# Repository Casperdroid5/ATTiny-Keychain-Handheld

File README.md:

# ATTiny Keychain Handheld

The ATTiny Keychain Handheld is an open-source project aimed at creating a compact and portable handheld device using the ATTiny microcontroller. This project provides a platform for hobbyists and electronics enthusiasts to build their own handheld device for various purposes such as gaming, basic applications, or custom projects.

## Features

- Compact and portable design
- ATTiny microcontroller
- OLED display
- User input
- Programmable
- Open-source

## Usage

To use the ATTiny Keychain Handheld, follow these steps:

1. Clone or download the project repository from [GitHub](https://github.com/Casperdroid5/ATTiny-Keychain-Handheld).
2. Gather the necessary components and tools required for building the handheld device.
3. Assemble the device following the step-by-step instructions provided in the documentation.
4. Upload the firmware code to the ATTiny microcontroller using the provided programming instructions.
5. Customize the device as desired by modifying the firmware code or the design files for the enclosure.

## Documentation

Detailed documentation and guides on how to build and customize the handheld device can be found in the [Documentation](https://github.com/Casperdroid5/ATTiny-Keychain-Handheld/tree/main/Documentation) directory of the project repository. The documentation includes component lists, PCB design and circuit diagrams.

## Contributing

Contributions to the ATTiny Keychain Handheld project are welcome. If you find any issues, have suggestions for improvements, or want to contribute new features, please refer to the [Contributing](https://github.com/Casperdroid5/ATTiny-Keychain-Handheld/tree/main/Contributing) directory in the project repository.

## License

The ATTiny Keychain Handheld project is released under the [MIT License](https://github.com/Casperdroid5/ATTiny-Keychain-Handheld/blob/main/LICENSE).

## Conclusion

The ATTiny Keychain Handheld project offers an exciting opportunity for electronics enthusiasts and hobbyists to build their own portable handheld device. With its compact design, ATTiny microcontroller, and open-source nature, the project provides a versatile platform for creating various applications and games. Whether you are a beginner or an experienced developer, this project encourages exploration and customization.

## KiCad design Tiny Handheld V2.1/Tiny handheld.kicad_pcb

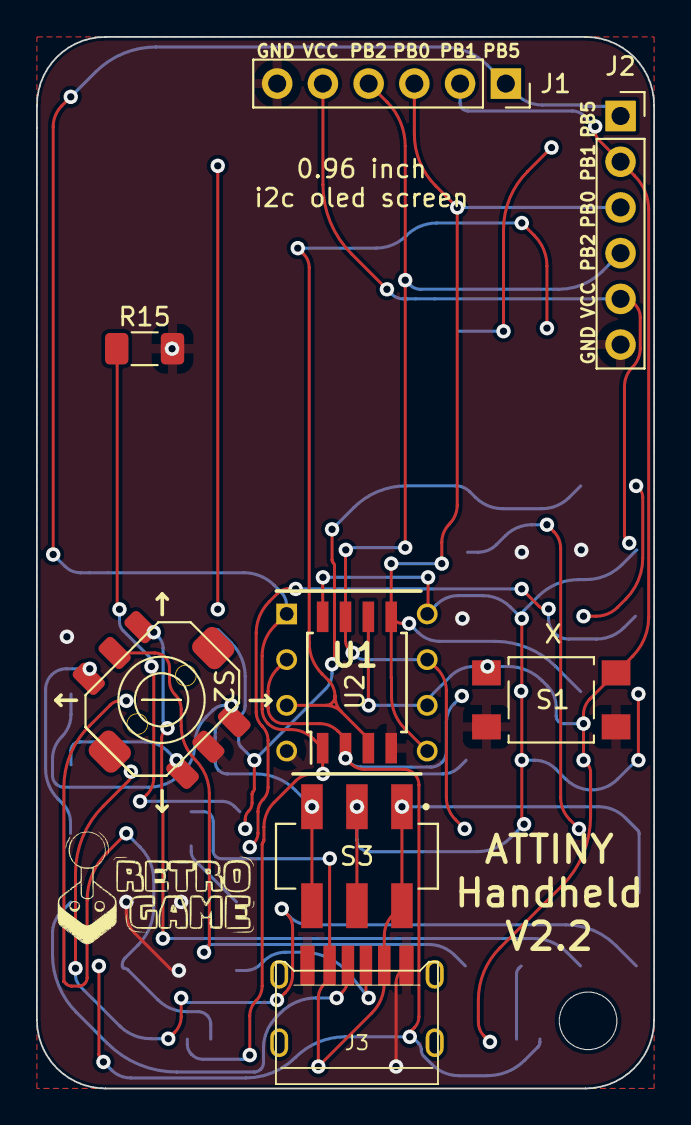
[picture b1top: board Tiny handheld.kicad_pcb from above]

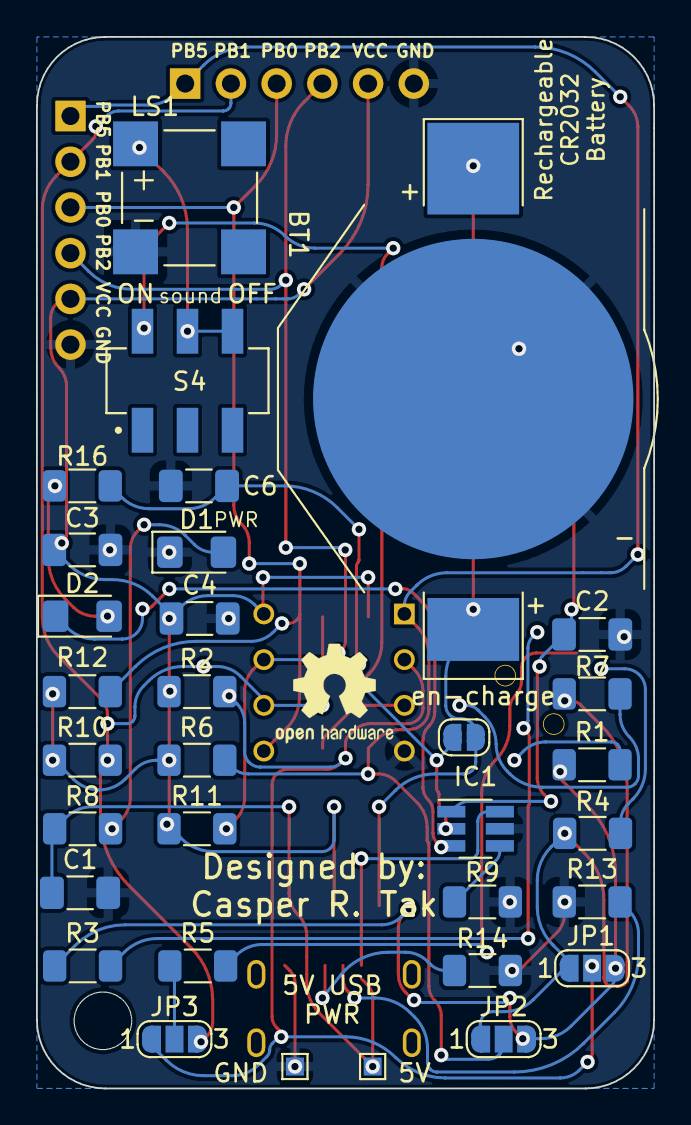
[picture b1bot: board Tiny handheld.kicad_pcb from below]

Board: 2 copper layers, 34.3 x 58.4 mm, 42 parts (32 on the bottom side), 27 nets.

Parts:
5V: 5V; TestPoint_Pad_1.0x1.0mm
BT1: Battery_Cell; BatteryHolder_Keystone_3002_1x2032
C1: 1uF 16V; C_1206_3216Metric_Pad1.33x1.80mm_HandSolder
C2: 1uF; C_1206_3216Metric_Pad1.33x1.80mm_HandSolder
C3: 47uF; C_1206_3216Metric_Pad1.33x1.80mm_HandSolder
C4: 100nF; C_1206_3216Metric_Pad1.33x1.80mm_HandSolder
C6: 2.2uF 16V; C_1206_3216Metric_Pad1.33x1.80mm_HandSolder
D1, D2: LED; LED_1206_3216Metric_Pad1.42x1.75mm_HandSolder
GND: GND; TestPoint_Pad_1.0x1.0mm
H1: MountingHole; MountingHole_3.2mm_M3
IC1: BQ21040DBVR; SOT-23-6_Handsoldering
J1: VDisplay/prog1; PinSocket_1x06_P2.54mm_Vertical
J2: HDisplay/prog; PinSocket_1x06_P2.54mm_Vertical
J3: USB_C_Receptacle_USB2.0; TYPE-C-31-M-17_handsolder
JP1, JP2, JP3: SolderJumper_3_Bridged123; SolderJumper-3_P1.3mm_Open_RoundedPad1.0x1.5mm_NumberLabels
LS1: KSSGK4B16-20; XDCR_KSSGK4B16-20
R1, R4: 88k; R_1206_3216Metric_Pad1.30x1.75mm_HandSolder
R2, R6: 22k; R_1206_3216Metric_Pad1.30x1.75mm_HandSolder
R3, R5, R7: 33k; R_1206_3216Metric_Pad1.30x1.75mm_HandSolder
R8, R16: 470; R_1206_3216Metric_Pad1.30x1.75mm_HandSolder
R9: 11k; R_1206_3216Metric_Pad1.30x1.75mm_HandSolder
R10: 10k; R_1206_3216Metric_Pad1.30x1.75mm_HandSolder
R11, R12: 4k7; R_1206_3216Metric_Pad1.30x1.75mm_HandSolder
R13, R14: 5k1; R_1206_3216Metric_Pad1.30x1.75mm_HandSolder
R15: 10k NTC; R_1206_3216Metric_Pad1.30x1.75mm_HandSolder
S1: MOMENTARY-SWITCH-SPST-2-SMD-5.2MM; SW_SPST_TL3305B
S2: JOYSTICK_MINI; 5 way button (joystick)
S3, S4: JS202011SCQN; SW_JS202011SCQN
U1: ATtiny85-20P; DIP781W56P254L950H533Q8N
U2: ATtiny85-20S; SOIC-8W_5.3x5.3mm_P1.27mm
en-charge: Jumper_2_Open; SolderJumper-2_P1.3mm_Open_RoundedPad1.0x1.5mm

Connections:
BatOut: BT1.1 (+), S3.3, S3.6, en-charge.2 (B)
ExtVCC: 5V.1, C1.1, IC1.6 (VIN), J3.A9 (VBUS), J3.B9 (VBUS), R8.1, S3.1, S3.4
GND: BT1.2 (-), C1.2, C2.2, C3.2, C4.2, C6.2, D1.1 (K), GND.1, IC1.5 (GND), J1.6, J2.6, J3.A12 (GND), J3.B12 (GND), LS1.N, R9.2, R13.1, R14.1, R15.2, S1.1, S1.2, S2.GND, U1.4 (GND), U2.4 (GND)
unnamed: C2.1, IC1.1 (TS), R15.1
unnamed: C6.1, IC1.2 (OUT), R16.1, en-charge.1 (A)
unnamed: D1.2 (A), R8.2
unnamed: D2.1 (K), IC1.3 (~CHG)
unnamed: D2.2 (A), R16.2
unnamed: IC1.4 (ISET), R9.1
unnamed: J3.A5 (CC1), R13.2
unnamed: J3.B5 (CC2), R14.2
unnamed: JP1.1 (A), JP2.1 (A), R4.1, R7.1
unnamed: JP1.3 (B), JP2.3 (B), R1.1, R3.1
unnamed: JP3.2 (C), R5.1
unnamed: LS1.P, S4.5, S4.6
unnamed: R1.2, S2.DOWN
unnamed: R3.2, S2.UP
unnamed: R4.2, S2.LEFT
unnamed: R5.2, S2.CTR (CENT)
unnamed: R7.2, S2.RIGHT
PB0/SDA/MOSI: J1.3, J2.3, R12.2, U1.5 (AREF/PB0), U2.5 (AREF/PB0)
PB1/MISO: J1.2, J2.2, JP3.3 (B), R10.2, S1.3, S1.4, U1.6 (PB1), U2.6 (PB1)
PB2/SCL/SCK: J1.4, J2.4, R11.2, U1.7 (PB2), U2.7 (PB2)
PB3: JP1.2 (C), JP3.1 (A), R2.2, U1.2 (XTAL1/PB3), U2.2 (XTAL1/PB3)
PB4: S4.4, U1.3 (XTAL2/PB4), U2.3 (XTAL2/PB4)
PB5/RES: J1.1, J2.1, JP2.2 (C), R6.2, U1.1 (~RESET/PB5), U2.1 (~RESET/PB5)
VCC: C3.1, C4.1, J1.5, J2.5, R2.1, R6.1, R10.1, R11.1, R12.1, S3.2, S3.5, U1.8 (VCC), U2.8 (VCC)

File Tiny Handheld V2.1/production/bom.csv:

Designator,Footprint,Quantity,Value,LCSC Part #
5V,TestPoint_Pad_1.0x1.0mm,1,5V,
BT1,BatteryHolder_Keystone_3002_1x2032,1,Battery_Cell,
C1,C_1206_3216Metric_Pad1.33x1.80mm_HandSolder,1,1uF 16V,
C2,C_1206_3216Metric_Pad1.33x1.80mm_HandSolder,1,1uF,
C3,C_1206_3216Metric_Pad1.33x1.80mm_HandSolder,1,47uF,
C4,C_1206_3216Metric_Pad1.33x1.80mm_HandSolder,1,100nF,
C6,C_1206_3216Metric_Pad1.33x1.80mm_HandSolder,1,2.2uF 16V,
"D1, D2",LED_1206_3216Metric_Pad1.42x1.75mm_HandSolder,2,LED,
GND,TestPoint_Pad_1.0x1.0mm,1,GND,
H1,MountingHole_3.2mm_M3,1,MountingHole,
IC1,SOT-23-6_Handsoldering,1,BQ21040DBVR,
J1,PinSocket_1x06_P2.54mm_Vertical,1,VDisplay/prog1,
J2,PinSocket_1x06_P2.54mm_Vertical,1,HDisplay/prog,
J3,TYPE-C-31-M-17_handsolder,1,USB_C_Receptacle_USB2.0,
"JP1, JP2, JP3",SolderJumper-3_P1.3mm_Open_RoundedPad1.0x1.5mm_NumberLabels,3,SolderJumper_3_Bridged123,
LS1,XDCR_KSSGK4B16-20,1,KSSGK4B16-20,
"R1, R4",R_1206_3216Metric_Pad1.30x1.75mm_HandSolder,2,88k,
R10,R_1206_3216Metric_Pad1.30x1.75mm_HandSolder,1,10k,
"R11, R12",R_1206_3216Metric_Pad1.30x1.75mm_HandSolder,2,4k7,
"R13, R14",R_1206_3216Metric_Pad1.30x1.75mm_HandSolder,2,5k1,
R15,R_1206_3216Metric_Pad1.30x1.75mm_HandSolder,1,10k NTC,
"R16, R8",R_1206_3216Metric_Pad1.30x1.75mm_HandSolder,2,470,
"R2, R6",R_1206_3216Metric_Pad1.30x1.75mm_HandSolder,2,22k,
"R3, R5, R7",R_1206_3216Metric_Pad1.30x1.75mm_HandSolder,3,33k,
R9,R_1206_3216Metric_Pad1.30x1.75mm_HandSolder,1,11k,
S1,SW_SPST_TL3305B,1,MOMENTARY-SWITCH-SPST-2-SMD-5.2MM,
S2,5 way button (joystick),1,JOYSTICK_MINI,
"S3, S4",SW_JS202011SCQN,2,JS202011SCQN,
U1,DIP781W56P254L950H533Q8N,1,ATtiny85-20P,
U2,SOIC-8W_5.3x5.3mm_P1.27mm,1,ATtiny85-20S,
en-charge,SolderJumper-2_P1.3mm_Open_RoundedPad1.0x1.5mm,1,Jumper_2_Open,

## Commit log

2022-09-16 First commit of tiny handheld
2022-09-16 designed custom 5 way button and finished up footprint assignment
2022-09-16 removed errors (ERC)
    Left warnings in
2022-09-16 added missing button footprint
2022-09-16 updated usb c port schematic
2022-09-16 updated footprint on attiny 85 and removed backup zip files
2022-09-16 fixed footprint error U2
    Changed the values back to the original
2022-09-16 added different switch in schematic
2022-09-16 fixed ERC error
2022-09-16 changed switch for audio toggle
2022-09-16 removed all errors from pcb new
    Ready to start pcb design
2022-09-16 changed speaker footprint and updated it
2022-09-16 first layout tryout
2022-09-16 layout improved
2022-09-16 improved layout and added silkscreen
2022-09-17 updated schematic (nothing special)
2022-09-17 removed vertical screen header
2022-09-17 started routing
2022-09-17 continued wiring
2022-09-17 more connections made
2022-09-17 all errors (that i found critical) resolved
2022-09-17 board cleanup
2022-09-17 first melted circuit tryout (rounded tracks)
2022-09-17 removed fluid traces, First functional design
2022-09-17 V1.0
    Added silkscreen and finished up with straight lines (no curves yet)
2022-09-17 Added curvy wires
    Because they are the best thing in this straight world
2022-09-17 updated page settings (kicad)
2022-09-17 gerber files added
2022-09-17 New gerber files
2022-09-17 Fixed gerber files
    can be uploaded directly to easyeda
2022-09-17 Cleanup
2022-10-06 Start on V2.0
    V1.0 could not be programmed easily via usb C, which was the whole point.
    Going back to arduino ISP programmer.
2022-10-06 New layout and silkscreen improvements
2022-10-06 finished silkscreen and component layout
2022-10-06 fixed screen orientation
2022-10-06 fixed screen orientation again
2022-10-06 added power testpoints
2022-10-06 Start Routing
2022-10-07 enh pcb layout and silkscreen
2022-10-08 started routing new PCB
2022-10-08 enh silkscreen
2022-10-08 wiring part 1
2022-10-08 completed routing, started erc
2022-10-08 ERC finished (with some exclusions)
2022-10-08 V2.0 Finished
2022-10-08 fames rounded tracks added
    added bom
2022-10-08 enh tracks
2022-10-10 Added V1.0 and v2.0 seperately
2022-10-31 started on V2.1, Fixed 5w-joystick
2022-10-31 stopped for now.
2022-11-21 enh v2.1
    - new 5 way button footprint (functional)
    - larger keyhole
    - rewired
2022-11-21 Improved silkscreen
2022-11-21 improved silkscreen and archieved 3d models
2022-11-21 Improved wiring spacing
2022-11-21 Created smooth traces version of V2.1
2022-11-28 small improvements V2.1
2022-12-04 V2.2 started (minor bug fixes)
2022-12-05 Fixed Silkscreen error
2022-12-05 added JY JX and JC to schematic
2023-03-11 Added games and potential oled driver
    Oled drivers need to be implemented
